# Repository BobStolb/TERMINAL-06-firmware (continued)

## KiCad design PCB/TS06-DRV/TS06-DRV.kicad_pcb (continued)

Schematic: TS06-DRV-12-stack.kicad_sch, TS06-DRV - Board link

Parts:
H1, H2, H3, H4, H5, H6, H7, H8: TS06_MountingHole_M3
XS11: PBS-10 female 2.54; TS06_PinSocket_1x10_R180
XS12: PBS-31 female 2.54; TS06_PinSocket_1x31_R270
XS21: PBS-5 female 2.54; TS06_PinSocket_1x05_R270
XS22: PBS-3 female 2.54; TS06_PinSocket_1x03_R270
XS23, XS24: PBS-4 female 2.54; TS06_PinSocket_1x04_R270
XS25: PBS-6 female 2.54; TS06_PinSocket_1x06_R270

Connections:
ANODE_AM: XS25.2; also elsewhere on the board
ANODE_H1: XS21.4; also elsewhere on the board
ANODE_H10: XS21.3; also elsewhere on the board
ANODE_M1: XS23.3; also elsewhere on the board
ANODE_M10: XS23.2; also elsewhere on the board
ANODE_PM: XS25.5; also elsewhere on the board
ANODE_S1: XS24.3; also elsewhere on the board
ANODE_S10: XS24.2; also elsewhere on the board
BL_A1: XS21.2; also elsewhere on the board
BL_A2: XS21.5; also elsewhere on the board
BL_A3: XS23.1; also elsewhere on the board
BL_A4: XS23.4; also elsewhere on the board
BL_A5: XS24.1; also elsewhere on the board
BL_A6: XS24.4; also elsewhere on the board
BL_A7: XS25.1; also elsewhere on the board
BL_A8: XS25.6; also elsewhere on the board
BL_K: XS21.1; also elsewhere on the board
CAT_A_KILO: XS12.25; also elsewhere on the board
CAT_A_MEGA: XS12.26; also elsewhere on the board
CAT_A_MICRO: XS12.31; also elsewhere on the board
CAT_A_MILLI: XS12.27; also elsewhere on the board
CAT_A_MINUS: XS12.29; also elsewhere on the board
CAT_A_NANO: XS12.22; also elsewhere on the board
CAT_A_P: XS12.30; also elsewhere on the board
CAT_A_PCT: XS12.23; also elsewhere on the board
CAT_A_PI: XS12.24; also elsewhere on the board
CAT_A_PLUS: XS12.28; also elsewhere on the board
CAT_B_AMP: XS12.14; also elsewhere on the board
CAT_B_FARAD: XS12.20; also elsewhere on the board
CAT_B_HENRY: XS12.18; also elsewhere on the board
CAT_B_HERTZ: XS12.19; also elsewhere on the board
CAT_B_OHM: XS12.15; also elsewhere on the board
CAT_B_SIEMENS: XS12.16; also elsewhere on the board
CAT_B_VOLT: XS12.17; also elsewhere on the board
CAT_B_WATT: XS12.21; also elsewhere on the board
COLON_L: XS22.2; also elsewhere on the board
COLON_RET: XS22.3; also elsewhere on the board
COLON_U: XS22.1; also elsewhere on the board
K0: XS11.9; also elsewhere on the board
K1: XS11.10; also elsewhere on the board
K2: XS11.8; also elsewhere on the board
K3: XS11.6; also elsewhere on the board
K4: XS11.4; also elsewhere on the board
K5: XS11.2; also elsewhere on the board
K6: XS11.1; also elsewhere on the board
K7: XS11.3; also elsewhere on the board
K8: XS11.5; also elsewhere on the board
K9: XS11.7; also elsewhere on the board
KS0: XS12.8; also elsewhere on the board
KS1: XS12.7; also elsewhere on the board
KS2: XS12.6; also elsewhere on the board
KS3: XS12.5; also elsewhere on the board
KS4: XS12.4; also elsewhere on the board
KS5: XS12.3; also elsewhere on the board
KS6: XS12.2; also elsewhere on the board
KS7: XS12.1; also elsewhere on the board
KS8: XS12.10; also elsewhere on the board
KS9: XS12.9; also elsewhere on the board
M_A: XS25.4; also elsewhere on the board

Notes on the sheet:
TS06-DRV · Board link
The display board carries male strips (XP) on its back and the driver board the mating female strips (XS); pin n of XPk mates pin n of XSk. XP11 carries the ИН-12 cathode bus, XP12 the ИН-17 bundle and both ИН-15, and XP21-XP25 the anodes, the colon and the LEDs.
XS12 (PBS-31 female 2.54, mates XP12)
XS11 (PBS-10 female 2.54, mates XP11)
XS21 (PBS-5 female 2.54, mates XP21)
XS22 (PBS-3 female 2.54, mates XP22)
XS23 (PBS-4 female 2.54, mates XP23)
XS24 (PBS-4 female 2.54, mates XP24)
XS25 (PBS-6 female 2.54, mates XP25)
Pin n of XPk (display board, male, on its back) mates pin n of XSk (driver board, female, on its face). The order of every strip is the order the display board's copper arrives in (tools/ts06pair.py HEADERS).
Standoff holes (M3): mechanical, no pad
Notes from tools/ts06pair.py
XS11..XS25: Board-to-board socket on the driver board's face towards the display; mates XP11, XP12, XP21, XP22, XP23, XP24, XP25 in turn.

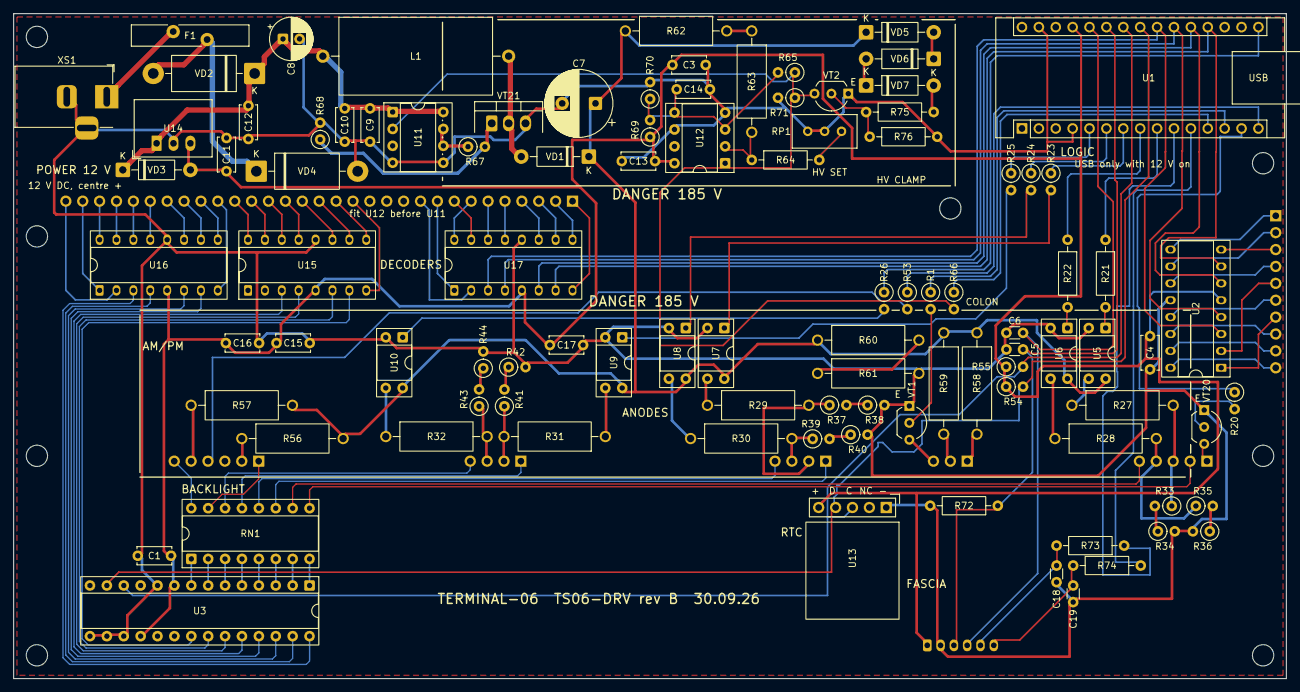
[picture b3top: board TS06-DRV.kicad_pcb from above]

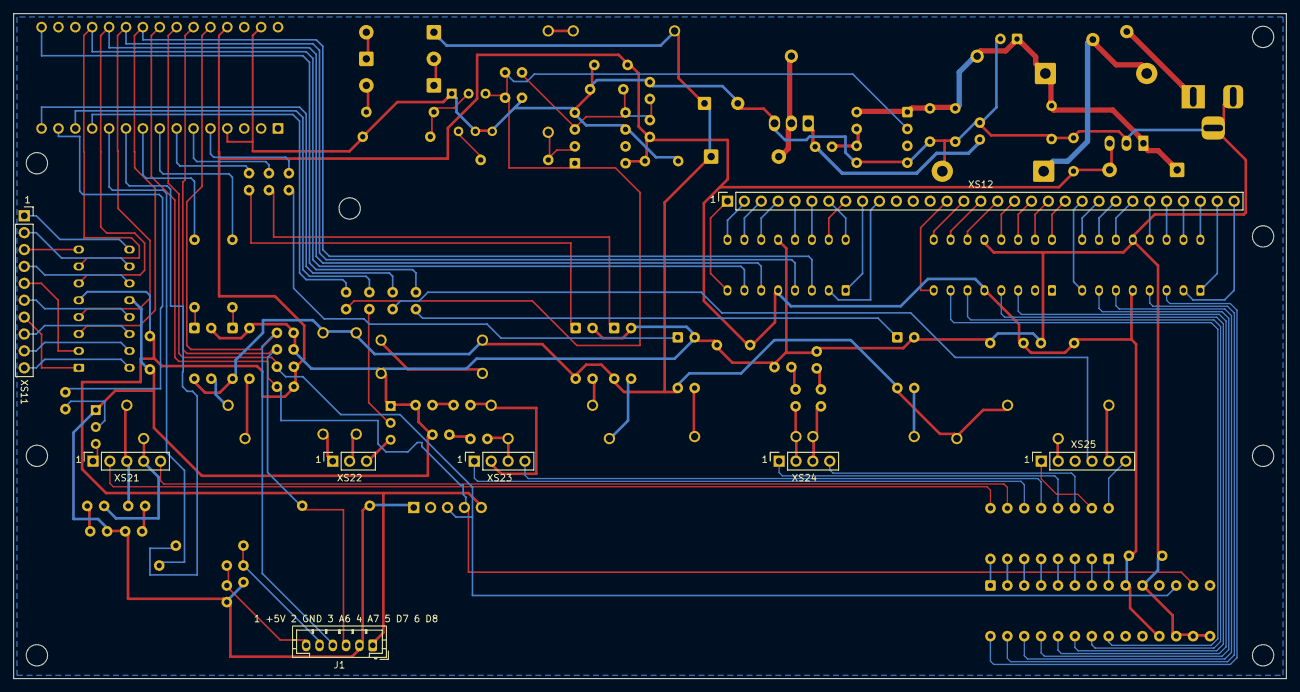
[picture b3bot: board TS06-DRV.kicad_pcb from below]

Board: 2 copper layers, 191.4 x 100.0 mm, 116 parts (8 on the bottom side), 136 nets.

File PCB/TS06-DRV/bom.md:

# TS06-DRV — bill of materials

Generated by `tools/bom_pair.py` from `tools/ts06pair.py`; do not edit by hand.
96 parts fitted, 12 footprints left empty. Every part is through-hole.

| Qty | Part | Value | Footprint | References |
|---|---|---|---|---|
| 1 | 5 V switching regulator | R-78E5.0-1.0 | TS06_R-78E_SIP3 | U14 |
| 1 | Arduino Nano | Arduino Nano | TS06_Arduino_Nano | U1 |
| 2 | Ceramic capacitor | 100n | TS06_C_Disc_P2.50mm | C5, C6 |
| 7 | Ceramic capacitor | 100n | TS06_C_Disc_P5.00mm | C1, C4, C13, C14, C15, C16, C17 |
| 2 | Ceramic capacitor | 10n | TS06_C_Disc_P2.50mm | C18, C19 |
| 2 | Ceramic capacitor | 10u | TS06_C_Disc_P5.00mm | C3, C11 |
| 1 | Ceramic capacitor | 10u 25V | TS06_C_Disc_P5.00mm | C10 |
| 2 | Ceramic capacitor | 1u 50V | TS06_C_Disc_P5.00mm | C9, C12 |
| 1 | Choke, axial, lying: **Bourns 5900-221-RC**, 220 µH ±10 %, Isat 1.8 A (Digi-Key; 1.89 A in another distributor's listing), Irated 1.6 A, DCR 0.162 Ω, Ø11.5 × 22.9 mm, Ø0.8 mm leads. The converter peaks at 1.18-1.44 A; no Ø12 radial of 220 µH reaches that (RLB1314-221KL 0.68 A) | 220u 1.8A 5900-221-RC | TS06_L_Axial_D11.5mm_L22.9mm_P27.94mm | L1 |
| 1 | DC jack | DC 5.5x2.1 | TS06_BarrelJack_Horizontal | XS1 |
| 1 | DS3231 mini module on a 5-way **PLS (male)** header: the module's own socket plugs on. Pad 1 (square) is GND; the module's + goes to pad 5 | DS3231 mini | TS06_PinHeader_1x05_DS3231 | U13 |
| 1 | Dual comparator | LM393 | TS06_DIP-8_W7.62mm_Socket | U12 |
| 1 | Electrolytic capacitor | 100u 25V | TS06_CP_Radial_D6.3mm_P2.50mm | C8 |
| 1 | Electrolytic capacitor | 4u7 400V | TS06_CP_Radial_D10.0mm_P5.00mm | C7 |
| 1 | Fast rectifier | HER106 / UF4007 | TS06_D_DO-41_P10.16mm | VD1 |
| 1 | I2C port expander | MCP23017-E/SP | TS06_DIP-28_W7.62mm_Socket | U3 |
| 1 | JST PH, vertical (top entry) | PH 6 vertical | TS06_JST_PH_B6B-PH-K_Vertical | J1 |
| 1 | MOSFET driver | TC4420 | TS06_DIP-8_W7.62mm_Socket | U11 |
| 1 | N-MOSFET 500 V | IRF840 | TS06_TO-220-3_Vertical_HV | VT21 |
| 2 | NPN 300 V | MPSA42 | TS06_TO-92_Inline_Wide | VT1, VT20 |
| 1 | NPN small-signal, TO-92, **E-B-C** (2N3904; not a BC547, which is C-B-E): the OV clamp | 2N3904 | TS06_TO-92_Inline_Wide | VT2 |
| 4 | Nixie decoder К155ИД1 | K155ID1 | TS06_DIP-16_W7.62mm_Socket_Oval | U2, U15, U16, U17 |
| 6 | Optocoupler, Darlington 300 V (TLP627 is obsolete: TLP627MF, from authorised stock) | TLP627 | TS06_DIP-4_W7.62mm_Socket | U5, U6, U7, U8, U9, U10 |
| 1 | PTC fuse, 1.1 A hold, radial, 5.1 mm leads (e.g. Bourns MF-R110; the footprint is the larger MF-RG1100 outline, which is an 11 A part) | PTC 1.1A | TS06_Fuse_PTC_MF-RG1100 | F1 |
| 1 | Resistor network, isolated, DIP-16 | 8x220R isolated DIP-16 | TS06_DIP-16_W7.62mm_Socket | RN1 |
| 1 | Resistor, 0.25 W | 100k | TS06_R_Axial_DIN0207_P10.16mm | R75 |
| 1 | Resistor, 0.25 W | 10R | TS06_R_Axial_DIN0207_P2.54mm_Vertical | R67 |
| 1 | Resistor, 0.25 W | 10k | TS06_R_Axial_DIN0207_P10.16mm | R76 |
| 3 | Resistor, 0.25 W | 10k | TS06_R_Axial_DIN0207_P2.54mm_Vertical | R1, R68, R71 |
| 2 | Resistor, 0.25 W | 10k 1% | TS06_R_Axial_DIN0207_P2.54mm_Vertical | R69, R70 |
| 1 | Resistor, 0.25 W | 18k 1% | TS06_R_Axial_DIN0207_P10.16mm | R64 |
| 1 | Resistor, 0.25 W | 1M | TS06_R_Axial_DIN0207_P10.16mm | R72 |
| 1 | Resistor, 0.25 W | 1M | TS06_R_Axial_DIN0207_P2.54mm_Vertical | R65 |
| 2 | Resistor, 0.25 W | 1k | TS06_R_Axial_DIN0207_P10.16mm | R73, R74 |
| 1 | Resistor, 0.25 W | 220R | TS06_R_Axial_DIN0207_P2.54mm_Vertical | R53 |
| 1 | Resistor, 0.25 W | 2k2 | TS06_R_Axial_DIN0207_P2.54mm_Vertical | R66 |
| 2 | Resistor, 0.25 W | 470R | TS06_R_Axial_DIN0207_P10.16mm | R21, R22 |
| 5 | Resistor, 0.25 W | 470R | TS06_R_Axial_DIN0207_P2.54mm_Vertical | R20, R23, R24, R25, R26 |
| 2 | Resistor, 0.25 W | 4k7 | TS06_R_Axial_DIN0207_P2.54mm_Vertical | R54, R55 |
| 2 | Resistor, 0.5 W 350 V: МЛТ-0,5 or С2-23-0,5 (body ≤ Ø4.2 × 10.8 mm, leads Ø0.8 mm; 1.1 mm holes at 15.24 mm) | 12k | TS06_R_Axial_MLT-0.5_P15.24mm | R31, R32 |
| 2 | Resistor, 0.5 W 350 V: МЛТ-0,5 or С2-23-0,5 (body ≤ Ø4.2 × 10.8 mm, leads Ø0.8 mm; 1.1 mm holes at 15.24 mm) | 18k | TS06_R_Axial_MLT-0.5_P15.24mm | R56, R57 |
| 2 | Resistor, 0.5 W 350 V: МЛТ-0,5 or С2-23-0,5 (body ≤ Ø4.2 × 10.8 mm, leads Ø0.8 mm; 1.1 mm holes at 15.24 mm) | 220k | TS06_R_Axial_MLT-0.5_P15.24mm | R58, R59 |
| 2 | Resistor, 0.5 W 350 V: МЛТ-0,5 or С2-23-0,5 (body ≤ Ø4.2 × 10.8 mm, leads Ø0.8 mm; 1.1 mm holes at 15.24 mm) | 470k | TS06_R_Axial_MLT-0.5_P15.24mm | R60, R61 |
| 4 | Resistor, 0.5 W 350 V: МЛТ-0,5 or С2-23-0,5 (body ≤ Ø4.2 × 10.8 mm, leads Ø0.8 mm; 1.1 mm holes at 15.24 mm) | 6k8 TBC | TS06_R_Axial_MLT-0.5_P15.24mm | R27, R28, R29, R30 |
| 2 | Resistor, 0.5 W 350 V: МЛТ-0,5 or С2-23-0,5 (body ≤ Ø4.2 × 10.8 mm, leads Ø0.8 mm; 1.1 mm holes at 15.24 mm) | 750k 1% | TS06_R_Axial_MLT-0.5_P15.24mm | R62, R63 |
| 1 | Schottky diode | 1N5822 | TS06_D_DO-201AD_P15.24mm | VD2 |
| 1 | Schottky diode, across U14 (5 V back-feed from USB) | 1N5819 | TS06_D_DO-41_P10.16mm | VD3 |
| 1 | Socket strip, straight (PBS), 8.5 mm | PBS-10 female 2.54 | TS06_PinSocket_1x10 | XS11 |
| 1 | Socket strip, straight (PBS), 8.5 mm | PBS-3 female 2.54 | TS06_PinSocket_1x03 | XS22 |
| 1 | Socket strip, straight (PBS), 8.5 mm | PBS-31 female 2.54 | TS06_PinSocket_1x31 | XS12 |
| 2 | Socket strip, straight (PBS), 8.5 mm | PBS-4 female 2.54 | TS06_PinSocket_1x04 | XS23, XS24 |
| 1 | Socket strip, straight (PBS), 8.5 mm | PBS-5 female 2.54 | TS06_PinSocket_1x05 | XS21 |
| 1 | Socket strip, straight (PBS), 8.5 mm | PBS-6 female 2.54 | TS06_PinSocket_1x06 | XS25 |
| 1 | TVS diode, unidirectional, 1500 W, DO-201 (1.5KE18A: VBR 17.1-18.9 V): trips F1 on a 19-24 V adapter | 1.5KE18A | TS06_D_DO-201AD_P15.24mm | VD4 |
| 1 | Trimmer, multi-turn | 5k | TS06_Trimmer_3296W | RP1 |
| 1 | Zener diode, 1 W, ±5 %, DO-41: the OV clamp's string (82 + 82 + 75 V, clamps 225-270 V) | 1N4761A | TS06_D_DO-41_P10.16mm | VD7 |
| 2 | Zener diode, 1 W, ±5 %, DO-41: the OV clamp's string (82 + 82 + 75 V, clamps 225-270 V) | 1N4762A | TS06_D_DO-41_P10.16mm | VD5, VD6 |

## Not fitted (DNP) unless the bench asks for them

| Qty | Part | Value | Footprint | References |
|---|---|---|---|---|
| 12 | Resistor, 0.25 W | 510k | TS06_R_Axial_DIN0207_P2.54mm_Vertical | R33, R34, R35, R36, R37, R38, R39, R40, R41, R42, R43, R44 |

## Hardware

| Qty | Item | For |
|---|---|---|
| 1 | DIP-28 socket, 300 mil (skinny) | U3 |
| 6 | DIP-4 socket, 300 mil | U5, U6, U7, U8, U9, U10 |
| 2 | DIP-8 socket, 300 mil | U11, U12 |
| 2 | Socket strip PBS-15, 2.54 mm | U1, the Nano stays removable |
| 4 | Mounting screw M3 + **nylon washer**, to the case | H5-H8, two into each cheek (tracks pass 2.2 mm from H5's centre) |
| 1 | Fascia lead, 6-way JST PH, 1:1, 180-200 mm: 2 × PHR-6 housings + 12 × SPH-002T-P0.5S crimps, or a ready-made lead. Pin 1 = +5V at both ends; beep it out before first power | J1 to the fascia's J1 |

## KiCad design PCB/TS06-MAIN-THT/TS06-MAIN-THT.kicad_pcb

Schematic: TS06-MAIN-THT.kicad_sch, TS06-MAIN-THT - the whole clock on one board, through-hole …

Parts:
C1, C2, C4, C5, C6, C13, C14: 100n; TS06_C_Disc_P2.50mm_Back
C3, C11: 10u; TS06_C_Disc_P5.00mm_Back
C7: 4u7 400V; TS06_CP_Radial_D8.0mm_P3.50mm_Back
C8: 100u 25V; TS06_CP_Radial_D6.3mm_P2.50mm_Back
C9, C12: 1u 50V; TS06_C_Disc_P5.00mm_Back
C10: 10u 25V; TS06_C_Disc_P5.00mm_Back
F1: PTC 1.1A; TS06_Fuse_Radial_MF-R_Back
HL1, HL2, HL3, HL4, HL5, HL6, HL7, HL8, HL9: amber 3mm; TS06_LED_D3.0mm
J1: PH 6; TS06_JST_PH_S6B-PH-K-S_Back
L1: 220u 2A; TS06_L_Radial_D10.0mm_P5.00mm_Back
R1, R2, R3, R4, R5, R6, R7, R8, R9, R10, R11, R12, R13, R14, R15, R16, R17, R18, R19, R68, R71: 10k; TS06_R_Axial_L6.3mm_P2.54mm_Vertical_Back
R20, R21, R22, R23, R24, R25, R26: 470R; TS06_R_Axial_L6.3mm_P2.54mm_Vertical_Back
R27, R28, R29, R30: 6k8 TBC; TS06_R_Axial_L9.9mm_P5.08mm_Vertical_Back
R31, R32: 12k; TS06_R_Axial_L9.9mm_P5.08mm_Vertical_Back
R33, R34, R35, R36, R37, R38, R39, R40, R41, R42, R43, R44: 510k DNP; TS06_R_Axial_L6.3mm_P2.54mm_Vertical_Back; not fitted
R45, R46, R47, R48, R49, R50, R51, R52, R53: 220R; TS06_R_Axial_L6.3mm_P2.54mm_Vertical_Back
R54, R55: 4k7; TS06_R_Axial_L6.3mm_P2.54mm_Vertical_Back
R56, R57: 8k2; TS06_R_Axial_L9.9mm_P5.08mm_Vertical_Back
R58, R59: 220k; TS06_R_Axial_L9.9mm_P5.08mm_Vertical_Back
R60, R61: 470k; TS06_R_Axial_L6.3mm_P2.54mm_Vertical_Back
R62, R63: 750k 1%; TS06_R_Axial_L6.3mm_P2.54mm_Vertical_Back
R64: 15k 1%; TS06_R_Axial_L6.3mm_P2.54mm_Vertical_Back
R65: 1M; TS06_R_Axial_L6.3mm_P2.54mm_Vertical_Back
R66: 2k2; TS06_R_Axial_L6.3mm_P2.54mm_Vertical_Back
R67: 10R; TS06_R_Axial_L6.3mm_P2.54mm_Vertical_Back
R69, R70: 10k 1%; TS06_R_Axial_L6.3mm_P2.54mm_Vertical_Back
RP1: 10k; TS06_Trimmer_3296W_Back
U1: Arduino Nano; TS06_Arduino_Nano_Back
U2: K155ID1; TS06_DIP-16_Back
U3, U4: MCP23017; TS06_DIP-28W_Back
U5, U6, U7, U8, U9, U10: TLP627; TS06_DIP-4_Back
U11: TC4420; TS06_DIP-8_Back
U12: LM393; TS06_DIP-8_Back
U13: DS3231 mini; TS06_PinHeader_1x05_Back
U14: R-78E5.0-1.0; TS06_R78E_SIP3_Back
V1, V2, V3, V4: IN-12A; TS06_IN12_Socket
V5, V6: IN-17; TS06_IN17_Socket
V7, V8: INS-1; TS06_INS1_Lamp
V9: IN-15B; TS06_IN12_Socket
V10: IN-15A; TS06_IN12_Socket
VD1: HER106; TS06_D_DO-41_P10.16mm_Back
VD2: 1N5822; TS06_D_DO-201_P15.24mm_Back
VT1, VT2, VT3, VT4, VT5, VT6, VT7, VT8, VT9, VT10, VT11, VT12, VT13, VT14, VT15, VT16, VT17, VT18, VT19, VT20: MPSA42; TS06_TO-92_Back
VT21: IRF840; TS06_TO-220_Horizontal_Back
XS1: DC 5.5x2.1; TS06_BarrelJack_Back

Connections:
+5V: C1.1, C2.1, C3.1, C4.1, C11.1, C13.1, J1.1, R45.1, R46.1, R47.1, R48.1, R49.1, R50.1, R51.1, R52.1, R54.1, R55.1, R69.1, U1.27 (+5V), U2.5 (VCC), U3.9 (VDD), U3.18 (RESET), U4.9 (VDD), U4.15 (A0), U4.18 (RESET), U12.8 (V+), U13.5 (+), U14.3 (OUT)
+12V: C8.1, C9.1, C10.1, C12.1, L1.1, U11.1 (VDD), U11.8 (VDD), U14.1 (IN), VD2.1 (K)
A0: U1.19 (A0), U2.7 (C 4)
A1: U1.20 (A1), U2.6 (B 2)
A2: U1.21 (A2), U2.4 (D 8)
A3: U1.22 (A3), U2.3 (A 1)
A6: C5.1, J1.3, U1.25 (A6)
A7: C6.1, J1.4, U1.26 (A7)
ANODE_AM: R56.1, V9.7
ANODE_H1: R28.2, R35.1, V2.7
ANODE_H10: R27.2, R33.1, V1.7
ANODE_M1: R30.2, R39.1, V4.7
ANODE_M10: R29.2, R37.1, V3.7
ANODE_PM: R57.1, V10.7
ANODE_S1: R32.2, R43.1, V6.A
ANODE_S10: R31.2, R41.1, V5.A
B1: R1.2, VT1.1 (B)
B2: R2.2, VT2.1 (B)
B3: R3.2, VT3.1 (B)
B4: R4.2, VT4.1 (B)
B5: R5.2, VT5.1 (B)
B6: R6.2, VT6.1 (B)
B7: R7.2, VT7.1 (B)
B8: R8.2, VT8.1 (B)
B9: R9.2, VT9.1 (B)
B10: R10.2, VT10.1 (B)
B11: R11.2, VT11.1 (B)
B12: R12.2, VT12.1 (B)
B13: R13.2, VT13.1 (B)
B14: R14.2, VT14.1 (B)
B15: R15.2, VT15.1 (B)
B16: R16.2, VT16.1 (B)
B17: R17.2, VT17.1 (B)
B18: R18.2, VT18.1 (B)
B19: R19.2, VT19.1 (B)
B20: R20.2, VT20.1 (B)
BLEED_H1: R35.2, R36.1
BLEED_H10: R33.2, R34.1
BLEED_HV: R60.2, R61.1
BLEED_M1: R39.2, R40.1
BLEED_M10: R37.2, R38.1
BLEED_S1: R43.2, R44.1
BLEED_S10: R41.2, R42.1
BL_A1: HL1.2 (A), R45.2
BL_A2: HL2.2 (A), R46.2
BL_A3: HL3.2 (A), R47.2
BL_A4: HL4.2 (A), R48.2
BL_A5: HL5.2 (A), R49.2
BL_A6: HL6.2 (A), R50.2
BL_A7: HL7.2 (A), R51.2
BL_A8: HL8.2 (A), R52.2
BL_K: HL1.1 (K), HL2.1 (K), HL3.1 (K), HL4.1 (K), HL5.1 (K), HL6.1 (K), HL7.1 (K), HL8.1 (K), VT20.3 (C)
CAT_A_KILO: V10.12, VT19.3 (C)
CAT_A_MEGA: V10.1, VT10.3 (C)
CAT_A_MICRO: V10.6, VT15.3 (C)
CAT_A_MILLI: V10.2, VT11.3 (C)
CAT_A_MINUS: V10.4, VT13.3 (C)
CAT_A_NANO: V10.9, VT16.3 (C)
CAT_A_P: V10.5, VT14.3 (C)
CAT_A_PCT: V10.10, VT17.3 (C)
CAT_A_PI: V10.11, VT18.3 (C)
CAT_A_PLUS: V10.3, VT12.3 (C)
CAT_B_AMP: V9.9, VT7.3 (C)
CAT_B_FARAD: V9.5, VT5.3 (C)
CAT_B_HENRY: V9.2, VT3.3 (C)
CAT_B_HERTZ: V9.3, VT4.3 (C)
CAT_B_OHM: V9.10, VT8.3 (C)
CAT_B_SIEMENS: V9.12, VT9.3 (C)
CAT_B_VOLT: V9.1, VT2.3 (C)
CAT_B_WATT: V9.6, VT6.3 (C)
COLON_L: R59.2, V8.1
COLON_RET: V7.2, V8.2, VT1.3 (C)
COLON_U: R58.2, V7.1
D2: R25.1, U1.5 (D2)
D3: R21.1, U1.6 (D3)
D4: R22.1, U1.7 (D4)
D5: R23.1, U1.8 (D5)
D6: R24.1, U1.9 (D6)
D7: J1.5, U1.10 (D7)
D8: J1.6, U1.11 (D8)
D9: R66.1, U1.12 (D9)
D10: R1.1, U1.13 (D10)
D11: R20.1, U1.14 (D11)
D12: R53.1, U1.15 (D12)
D13: R26.1, U1.16 (D13)
EMIT_H1: R28.1, U6.3 (E)
EMIT_H10: R27.1, U5.3 (E)
EMIT_M1: R30.1, U8.3 (E)
EMIT_M10: R29.1, U7.3 (E)
EMIT_S1: R32.1, U10.3 (E)
EMIT_S10: R31.1, U9.3 (E)
FB: R63.2, R64.1, U12.2 (IN1-)
FB_LOW: R64.2, RP1.1
FB_MID: R62.2, R63.1
GATE: R67.2, R68.1, VT21.1 (G)
GATE_D: R67.1, U11.6 (OUT), U11.7 (OUT)
GND: C1.2, C2.2, C3.2, C4.2, C5.2, C6.2, C7.2, C8.2, C9.2, C10.2, C11.2, C12.2, C13.2, C14.2, HL9.1 (K), J1.2, R34.2, R36.2, R38.2, R40.2, R42.2, R44.2, R61.2, R68.2, R70.2, R71.2, RP1.2 (W), RP1.3, U1.4 (GND), U1.29 (GND), U2.12 (GND), U3.10 (VSS), U3.15 (A0), U3.16 (A1), U3.17 (A2), U4.10 (VSS), U4.16 (A1), U4.17 (A2), U5.2 (K), U6.2 (K), U7.2 (K), U8.2 (K), U9.2 (K), U10.2 (K), U11.4 (GND), U11.5 (GND), U12.4 (GND), U12.6 (IN2-), U13.1 (-), U14.2 (GND), VT1.2 (E), VT2.2 (E), VT3.2 (E), VT4.2 (E), VT5.2 (E), VT6.2 (E), VT7.2 (E), VT8.2 (E), VT9.2 (E), VT10.2 (E), VT11.2 (E), VT12.2 (E), VT13.2 (E), VT14.2 (E), VT15.2 (E), VT16.2 (E), VT17.2 (E), VT18.2 (E), VT19.2 (E), VT20.2 (E), VT21.3 (S), XS1.2 (-)
HV185: C7.1, R56.2, R57.2, R58.1, R59.1, R60.1, R62.1, U5.4 (C), U6.4 (C), U7.4 (C), U8.4 (C), U9.4 (C), U10.4 (C), VD1.1 (K)
K0: U2.10 (Q7), V1.6, V2.6, V3.6, V4.6, V5.0, V6.0
K1: U2.9 (Q3), V1.9, V2.9, V3.9, V4.9, V5.1, V6.1
K2: U2.11 (Q6), V1.10, V2.10, V3.10, V4.10, V5.2, V6.2
K3: U2.13 (Q4), V1.11, V2.11, V3.11, V4.11, V5.3, V6.3
K4: U2.15 (Q1), V1.12, V2.12, V3.12, V4.12, V5.4, V6.4
K5: U2.2 (Q9), V1.1, V2.1, V3.1, V4.1, V5.5, V6.5
K6: U2.1 (Q8), V1.2, V2.2, V3.2, V4.2, V5.6, V6.6
K7: U2.16 (Q0), V1.3, V2.3, V3.3, V4.3, V5.7, V6.7
K8: U2.14 (Q5), V1.4, V2.4, V3.4, V4.4, V5.8, V6.8
K9: U2.8 (Q2), V1.5, V2.5, V3.5, V4.5, V5.9, V6.9
M_A: HL9.2 (A), R53.2
OPT_H1: R22.2, U6.1 (A)
OPT_H10: R21.2, U5.1 (A)
OPT_M1: R24.2, U8.1 (A)
OPT_M10: R23.2, U7.1 (A)
OPT_S1: R26.2, U10.1 (A)
OPT_S10: R25.2, U9.1 (A)
PWM_G: R65.1, R66.2, R71.1, U11.2 (IN), U12.1 (OUT1)
SCL: R55.2, U1.24 (A5/SCL), U3.12 (SCL), U4.12 (SCL), U13.3 (C)
SDA: R54.2, U1.23 (A4/SDA), U3.13 (SDA), U4.13 (SDA), U13.4 (D)
SW: L1.2, VD1.2 (A), VT21.2 (D)
U3_GPA0: R2.1, U3.21 (GPA0)
U3_GPA1: R3.1, U3.22 (GPA1)
U3_GPA2: R4.1, U3.23 (GPA2)
U3_GPA3: R5.1, U3.24 (GPA3)
U3_GPA4: R6.1, U3.25 (GPA4)
U3_GPA5: R7.1, U3.26 (GPA5)
U3_GPA6: R8.1, U3.27 (GPA6)
U3_GPA7: R9.1, U3.28 (GPA7)
U4_GPA0: R10.1, U4.21 (GPA0)
U4_GPA1: R11.1, U4.22 (GPA1)
U4_GPA2: R12.1, U4.23 (GPA2)
U4_GPA3: R13.1, U4.24 (GPA3)
U4_GPA4: R14.1, U4.25 (GPA4)
U4_GPA5: R15.1, U4.26 (GPA5)
U4_GPA6: R16.1, U4.27 (GPA6)
U4_GPA7: R17.1, U4.28 (GPA7)
U4_GPB0: R18.1, U4.1 (GPB0)
U4_GPB1: R19.1, U4.2 (GPB1)
VIN_F: F1.2, VD2.2 (A)
VIN_J: F1.1, XS1.1 (+)
VREF: C14.1, R65.2, R69.2, R70.1, U12.3 (IN1+), U12.5 (IN2+)

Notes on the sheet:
12 V IN. Barrel jack, PTC fuse, reverse-polarity Schottky, then an R-78E switching regulator makes the 5 V rail for everything, Nano included (its 5V pin; VIN open). A PC on the Nano's USB with no adapter plugged in runs the logic with the tubes dark - the boost has no 12 V.
185 V RAIL, regulated this time. D9's 31 kHz clock reaches the MOSFET through a proper 12 V driver; a comparator watches the rail through a 1.5 M / 20.5 k divider and holds the driver input low whenever FB is above VREF, so the stage skips cycles until the rail sags back. The trimmer is a rheostat 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
NANO. Pin map is the firmware's and is not renumbered.
ONE DECODER for six digit tubes. A0..A3 -> C B D A as on the inherited board; output Q_c goes to the cathode of digit d where digitMask[d] = c (BOARD_TYPE 0), so K7 hangs off Q0, K4 off Q1 ... K5 off Q9.
SIX DIGIT TUBES on the shared cathode bus K0..K9 (named by digit). IN-12A pads per the inherited copper: pad 7 anode, pad 8 no pin. IN-17 pads named by digit from judge2005's footprint - bench gate 3.
ANODE CHAINS, one per digit tube: Nano pin -> 470 R -> TLP627 LED; collector on HV185, emitter -> series R -> anode. Bleed pairs are DNP unless the bench asks for them. 6k8 for the IN-12s is TBC (gate 2).
AM/PM: two MCP23017 on the same I2C wires as the RTC, eighteen 300 V low-side switches, one per real cathode. V9 IN-15B shows A, V10 IN-15A shows P. Anode resistors one per tube. Pad maps: bench gate 4.
COLON: two INS-1 neons, each with its own 220 k ballast, one low-side MPSA42 on D10.
BACKLIGHT: eight amber LEDs, one under each tube, series 220 R from +5V, switched low-side from D11. The 'm' of AM/PM is HL9 straight off D12: firmware decides always-on or 12-hour-only.
FASCIA CABLE J1, pin order fixed for both fascia builds: +5V GND A6 A7 D7 D8. The 100 nF ladder filters sit here, at the board end.
RTC. SMD build: DS3231SN with a CR2032 holder. THT build: the DS3231 mini module on a 5-way header (- NC C D +).

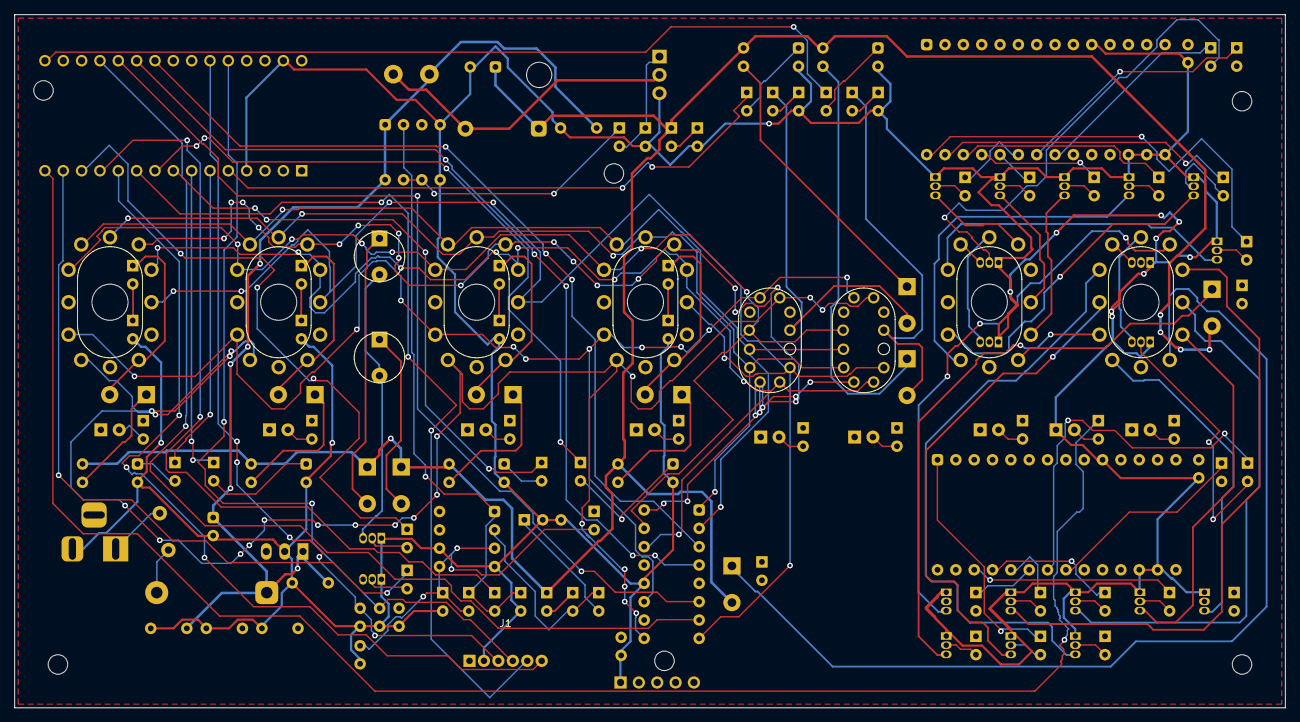
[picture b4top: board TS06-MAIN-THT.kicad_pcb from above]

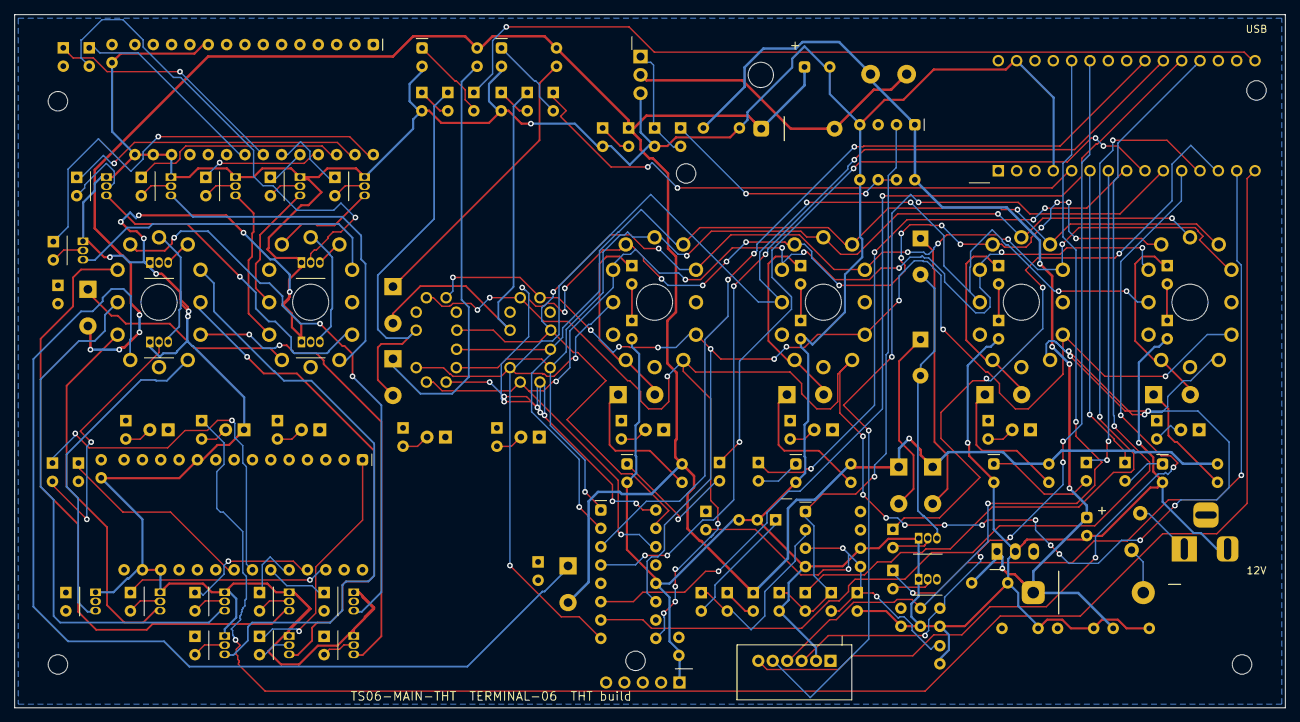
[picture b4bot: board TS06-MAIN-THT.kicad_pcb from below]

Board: 2 copper layers, 176.0 x 96.0 mm, 146 parts (127 on the bottom side), 140 nets.

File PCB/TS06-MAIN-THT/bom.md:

# TS06-MAIN-THT — bill of materials

Generated by `tools/bom_main.py --tht` from `tools/ts06main.py`; do not edit by hand.
134 parts fitted, 12 footprints left empty.

| Qty | Part | Value | Footprint | References |
|---|---|---|---|---|
| 1 | Arduino Nano | Arduino Nano | TS06_Arduino_Nano_Back | U1 |
| 7 | Capacitor | 100n | TS06_C_Disc_P2.50mm_Back | C1, C2, C4, C5, C6, C13, C14 |
| 1 | Capacitor | 100u 25V | TS06_CP_Radial_D6.3mm_P2.50mm_Back | C8 |
| 2 | Capacitor | 10u | TS06_C_Disc_P5.00mm_Back | C3, C11 |
| 1 | Capacitor | 10u 25V | TS06_C_Disc_P5.00mm_Back | C10 |
| 2 | Capacitor | 1u 50V | TS06_C_Disc_P5.00mm_Back | C9, C12 |
| 1 | Capacitor | 4u7 400V | TS06_CP_Radial_D8.0mm_P3.50mm_Back | C7 |
| 1 | JST PH connector, 6-way | PH 6 | TS06_JST_PH_S6B-PH-K-S_Back | J1 |
| 1 | Fast rectifier | HER106 | TS06_D_DO-41_P10.16mm_Back | VD1 |
| 1 | Schottky diode | 1N5822 | TS06_D_DO-201_P15.24mm_Back | VD2 |
| 1 | PTC fuse | PTC 1.1A | TS06_Fuse_Radial_MF-R_Back | F1 |
| 1 | DC jack | DC 5.5x2.1 | TS06_BarrelJack_Back | XS1 |
| 1 | Nixie decoder К155ИД1 | K155ID1 | TS06_DIP-16_Back | U2 |
| 1 | Inductor | 220u 2A | TS06_L_Radial_D10.0mm_P5.00mm_Back | L1 |
| 9 | LED, amber 3 mm | amber 3mm | TS06_LED_D3.0mm | HL1, HL2, HL3, HL4, HL5, HL6, HL7, HL8, HL9 |
| 1 | Dual comparator | LM393 | TS06_DIP-8_Back | U12 |
| 2 | Neon lamp ИНС-1 | INS-1 | TS06_INS1_Lamp | V7, V8 |
| 2 | I2C port expander | MCP23017 | TS06_DIP-28W_Back | U3, U4 |
| 1 | N-MOSFET 500 V | IRF840 | TS06_TO-220_Horizontal_Back | VT21 |
| 20 | NPN 300 V | MPSA42 | TS06_TO-92_Back | VT1, VT2, VT3, VT4, VT5, VT6, VT7, VT8, VT9, VT10, VT11, VT12, VT13, VT14, VT15, VT16, VT17, VT18, VT19, VT20 |
| 1 | Resistor | 10R | TS06_R_Axial_L6.3mm_P2.54mm_Vertical_Back | R67 |
| 21 | Resistor | 10k | TS06_R_Axial_L6.3mm_P2.54mm_Vertical_Back | R1, R2, R3, R4, R5, R6, R7, R8, R9, R10, R11, R12, R13, R14, R15, R16, R17, R18, R19, R68, R71 |
| 2 | Resistor | 10k 1% | TS06_R_Axial_L6.3mm_P2.54mm_Vertical_Back | R69, R70 |
| 2 | Resistor | 12k | TS06_R_Axial_L9.9mm_P5.08mm_Vertical_Back | R31, R32 |
| 1 | Resistor | 15k 1% | TS06_R_Axial_L6.3mm_P2.54mm_Vertical_Back | R64 |
| 1 | Resistor | 1M | TS06_R_Axial_L6.3mm_P2.54mm_Vertical_Back | R65 |
| 9 | Resistor | 220R | TS06_R_Axial_L6.3mm_P2.54mm_Vertical_Back | R45, R46, R47, R48, R49, R50, R51, R52, R53 |
| 2 | Resistor | 220k | TS06_R_Axial_L9.9mm_P5.08mm_Vertical_Back | R58, R59 |
| 1 | Resistor | 2k2 | TS06_R_Axial_L6.3mm_P2.54mm_Vertical_Back | R66 |
| 7 | Resistor | 470R | TS06_R_Axial_L6.3mm_P2.54mm_Vertical_Back | R20, R21, R22, R23, R24, R25, R26 |
| 2 | Resistor | 470k | TS06_R_Axial_L6.3mm_P2.54mm_Vertical_Back | R60, R61 |
| 2 | Resistor | 4k7 | TS06_R_Axial_L6.3mm_P2.54mm_Vertical_Back | R54, R55 |
| 4 | Resistor | 6k8 TBC | TS06_R_Axial_L9.9mm_P5.08mm_Vertical_Back | R27, R28, R29, R30 |
| 2 | Resistor | 750k 1% | TS06_R_Axial_L6.3mm_P2.54mm_Vertical_Back | R62, R63 |
| 2 | Resistor | 8k2 | TS06_R_Axial_L9.9mm_P5.08mm_Vertical_Back | R56, R57 |
| 1 | RTC module | DS3231 mini | TS06_PinHeader_1x05_Back | U13 |
| 1 | 5 V switching regulator | R-78E5.0-1.0 | TS06_R78E_SIP3_Back | U14 |
| 1 | MOSFET driver | TC4420 | TS06_DIP-8_Back | U11 |
| 6 | Optocoupler, Darlington | TLP627 | TS06_DIP-4_Back | U5, U6, U7, U8, U9, U10 |
| 1 | Trimmer | 10k | TS06_Trimmer_3296W_Back | RP1 |
| 4 | Nixie tube | IN-12A | TS06_IN12_Socket | V1, V2, V3, V4 |
| 1 | Nixie tube | IN-15A | TS06_IN12_Socket | V10 |
| 1 | Nixie tube | IN-15B | TS06_IN12_Socket | V9 |
| 2 | Nixie tube | IN-17 | TS06_IN17_Socket | V5, V6 |

## Not fitted (DNP) unless the bench asks for them

| Qty | Part | Value | Footprint | References |
|---|---|---|---|---|
| 12 | Resistor | 510k | TS06_R_Axial_L6.3mm_P2.54mm_Vertical_Back | R33, R34, R35, R36, R37, R38, R39, R40, R41, R42, R43, R44 |

## What this board adds and removes against the three it replaces

Compared with the inherited AlexGyver board + TS06-SEC + TS06-COLON, one TS06-MAIN unit needs:

* **new:** the 12 V input stage (jack, PTC, Schottky, 100 µF), an R-78E5.0-1.0 regulator, a TC4420 driver, an LM393 comparator and the rail divider with its trimmer, one anode resistor per digit tube (six), four more TLP627 (six in all instead of the inherited four plus SEC's two), two more backlight LEDs (eight), and in the SMD build a bare DS3231SN with a CR2032 holder;
* **unchanged in kind:** the Nano, the К155ИД1, the two MCP23017 and eighteen MPSA42/MMBTA42 with their base resistors, the two ИНС-1 with their own 220 kΩ ballasts, the eight tubes, the fascia connector;
* **gone:** the inherited board itself, SEC's XS1/XS2/XS3/XS4 and the colon board's connector and harnesses, the 470 kΩ bleed trimmer and the shared 10 kΩ anode resistor of the old converter.

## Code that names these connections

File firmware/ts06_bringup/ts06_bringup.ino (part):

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#include <avr/pgmspace.h>

#define BAUD      9600
#define PIN_HV    9       // D9 -> R66 -> PWM_G -> TC4420 -> IRF840: the converter's clock
#define PIN_COLON 10      // D10 -> R1 10k -> VT1 base: both colon lamps
#define PIN_BACKL 11      // D11 -> R20 470R -> VT20 base: BL_K, every LED's cathode
#define PIN_M     12      // D12 -> R53 220R -> HL9, the "m" LED
#define PIN_MINUS 7       // fascia "-" button, to ground
#define PIN_PLUS  8       // fascia "+" button, to ground
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  else if (ledState >= 2 && ledState <= 9) b = 1 << (ledState - 2);
  mcpWrite(0x13, b);
  digitalWrite(PIN_M, (ledState == 1 || ledState == 10) ? HIGH : LOW);
  digitalWrite(PIN_BACKL, ledState ? HIGH : LOW);   // VT20 grounds BL_K
  Serial.print(F("LEDs: "));
  if (ledState == 0) Serial.println(F("off"));
  else if (ledState == 1) Serial.println(F("all nine on (VT20 on, GPB0-7 high, D12 high)"));
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  }
  Serial.print(n); Serial.println(F(" device(s)"));
  if (!mcp) Serial.println(F("  0x20 MISSING: U3 not fitted, turned round, or no +5 V on its pin 9"));
  if (!rtc) Serial.println(F("  0x68 MISSING: the module not fitted, or its pins in another order (gate 6: - NC C D +)"));
  if (mcp) {
    mcpInit();
    applyLeds();
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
